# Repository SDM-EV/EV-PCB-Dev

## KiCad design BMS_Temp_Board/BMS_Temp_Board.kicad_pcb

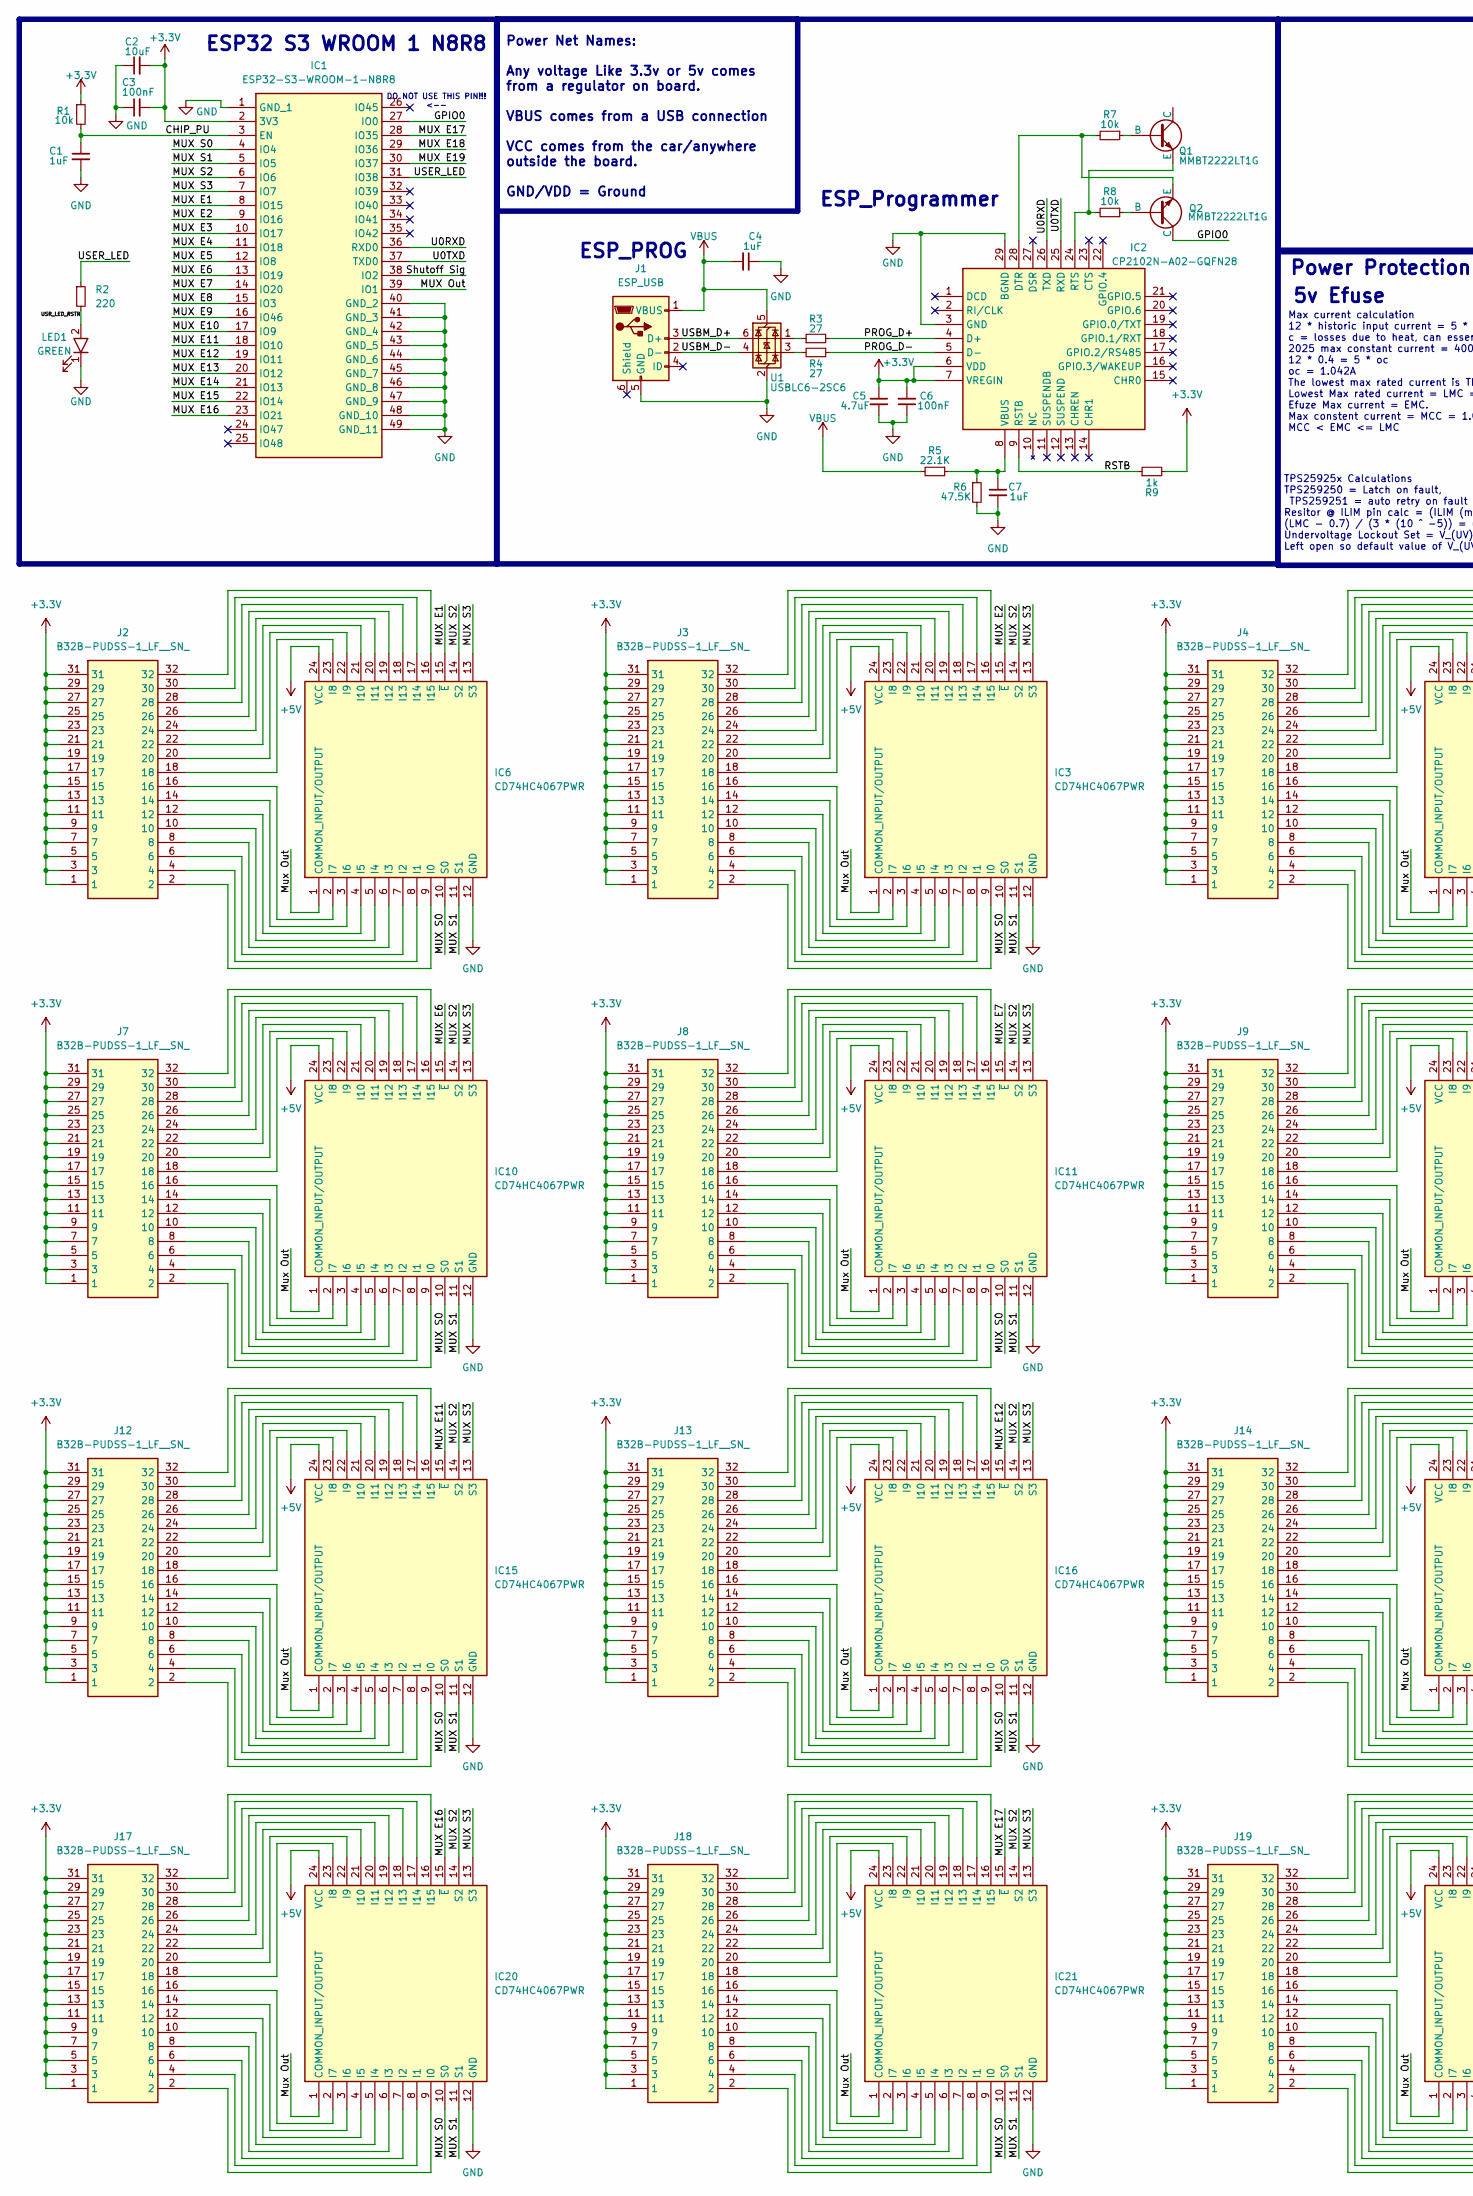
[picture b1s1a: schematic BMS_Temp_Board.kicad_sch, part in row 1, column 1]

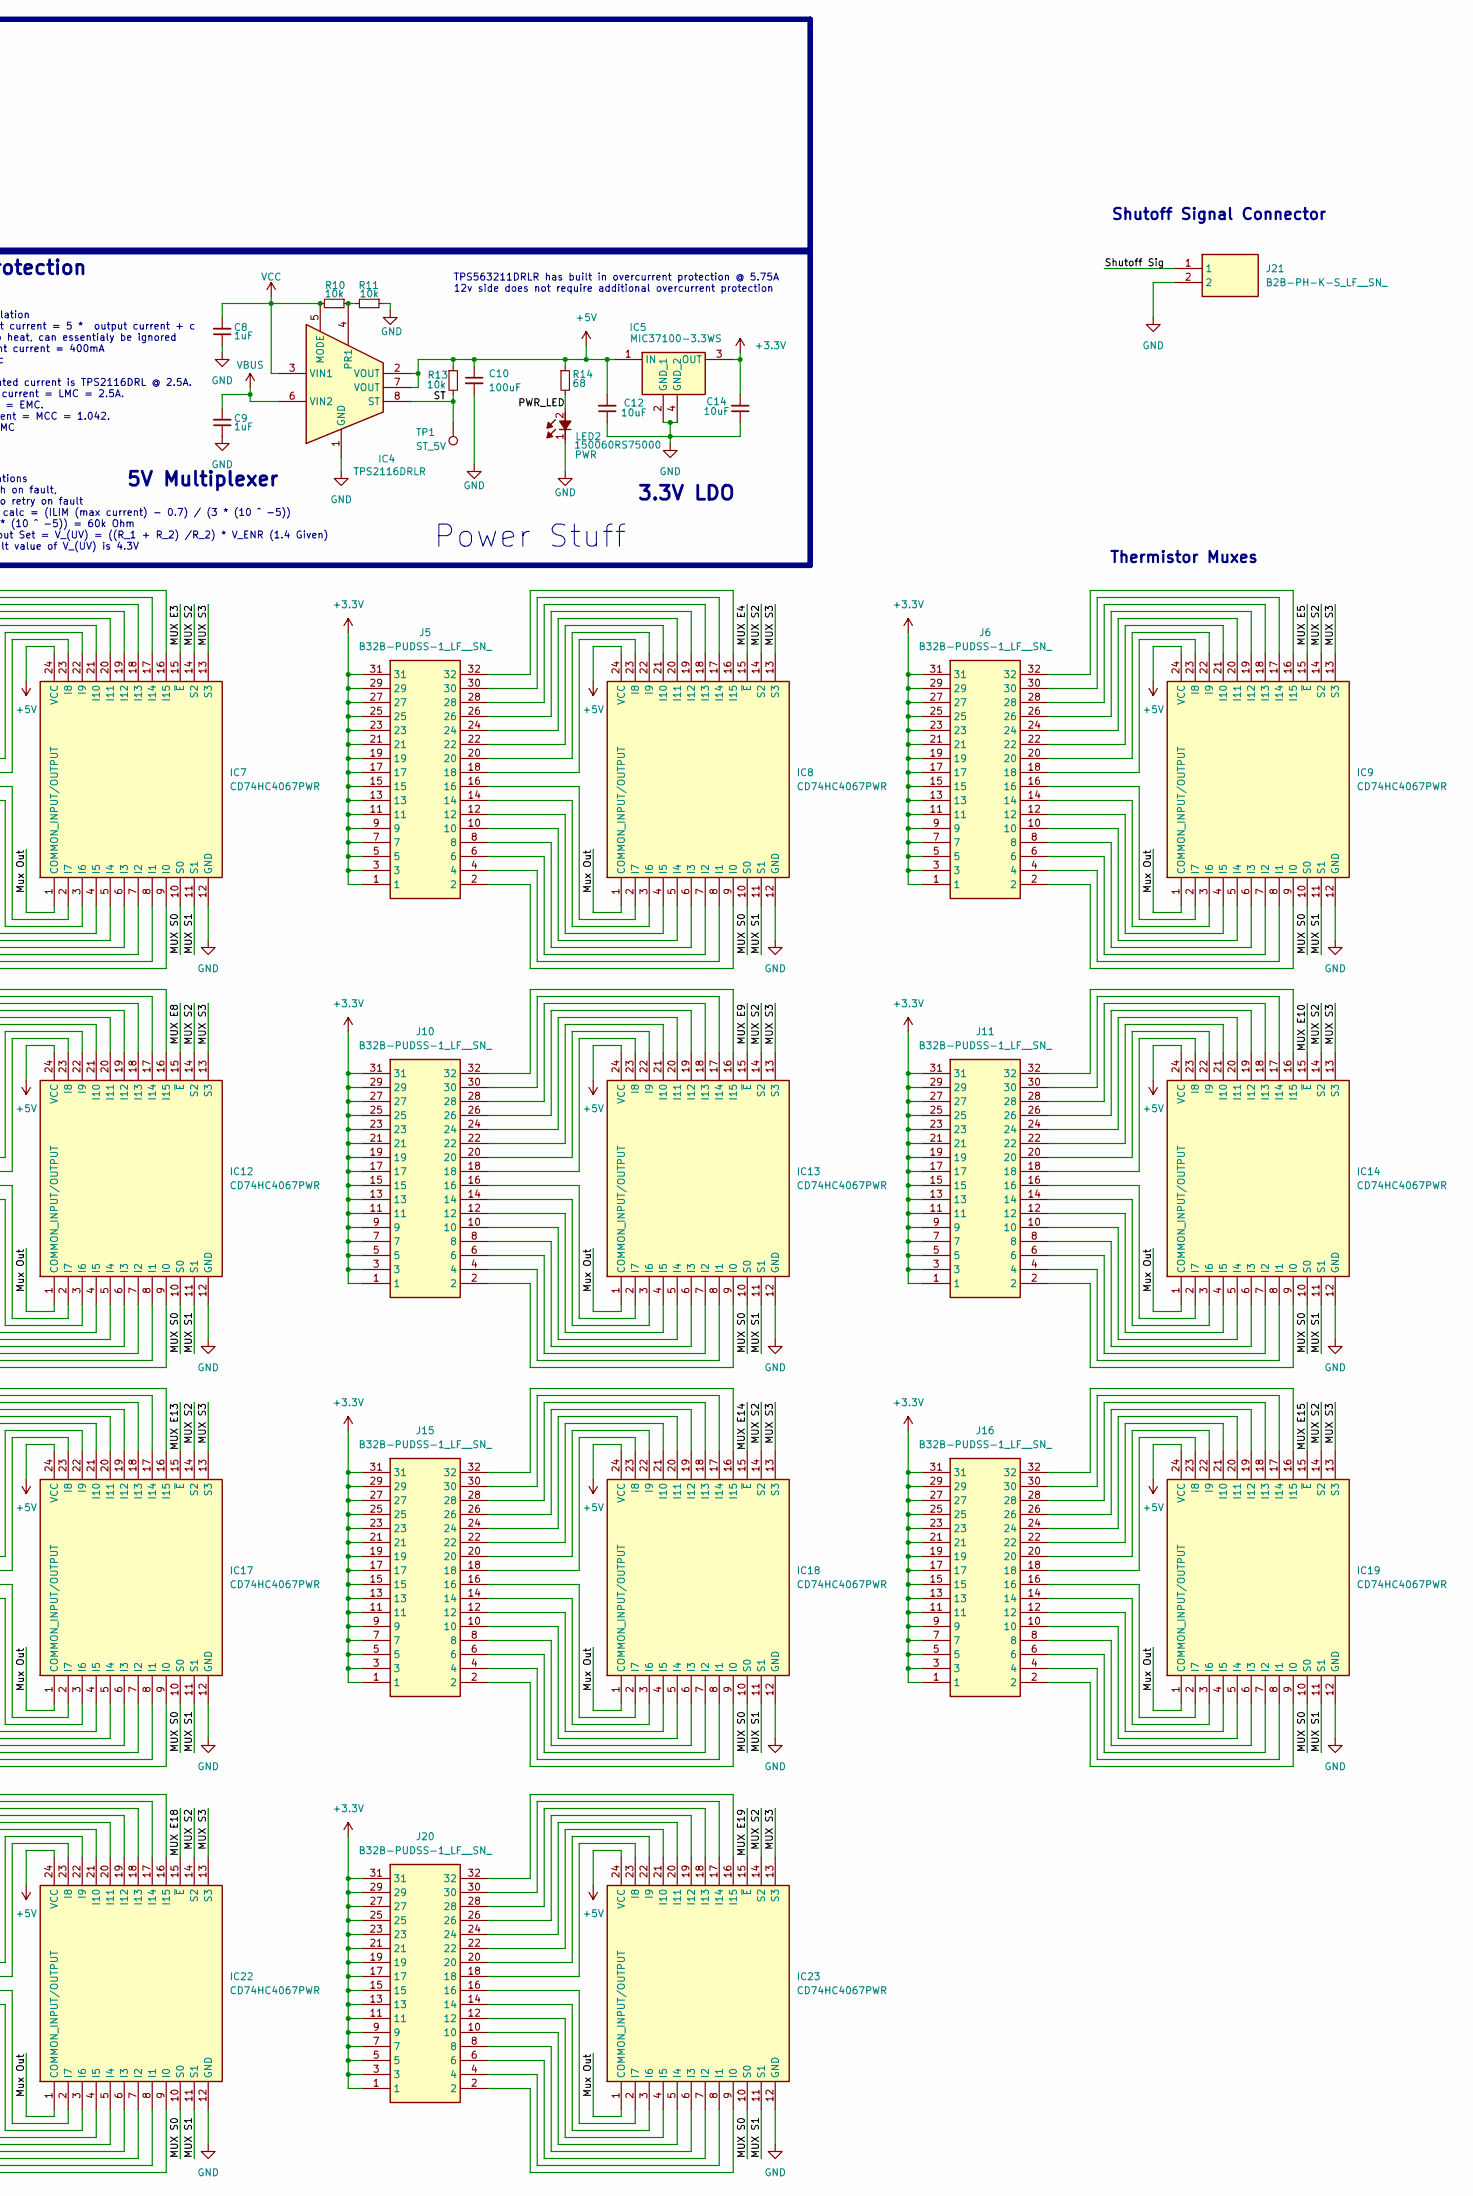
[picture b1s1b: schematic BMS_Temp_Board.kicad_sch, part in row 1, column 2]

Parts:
C1, C4, C7, C8, C9: 1uF; C_0603_1608Metric
C2, C12, C14: 10uF; C_0603_1608Metric
C3, C6: 100nF; C_0603_1608Metric
C5: 4.7uF; C_0603_1608Metric
C10: 100uF; C_0603_1608Metric
IC1: ESP32-S3-WROOM-1-N8R8; ESP32S3WROOM1N8R8; Mouser Part Number 356-EP32S3WROOM1N8R8
IC2: CP2102N-A02-GQFN28; QFN50P500X500X80-29N-D; Mouser Part Number 634-CP2102NA02GQFN28
IC3, IC6, IC7, IC8, IC9, IC10, IC11, IC12, IC13, IC14, IC15, IC16, IC17, IC18, IC19, IC20, IC21, IC22, IC23: CD74HC4067PWR; SOP65P640X120-24N; Manufacturer_Part_Number CD74HC4067PWR
IC4: TPS2116DRLR; SOTFL50P160X60-8L; Mouser Part Number 595-TPS2116DRLR
IC5: MIC37100-3.3WS; SOT230P700X180-4N; Mouser Part Number 998-MIC37100-3.3WS
J1: ESP_USB; USB_Micro-B_Molex-105017-0001
J2, J3, J4, J5, J6, J7, J8, J9, J10, J11, J12, J13, J14, J15, J16, J17, J18, J19, J20: B32B-PUDSS-1_LF__SN_; B32BPUDSS1LFSN; Mouser Part Number 306-B32BPUDSS1LFSN
J21: B2B-PH-K-S_LF__SN_; SHDR2W50P0X200_1X2_590X450X600P; Mouser Part Number 306-B2BPHKSLFSNPP
LED1: GREEN; LED_0603_1608Metric; Mouser Part Number 720-P4112S2U1252X4X5
LED2: 150060RS75000; LEDC1608X80N; Mouser Part Number 710-150060RS75000
Q1, Q2: MMBT2222LT1G; SOT96P237X111-3N
R1, R7, R8, R10, R11, R13: 10k; R_0603_1608Metric
R2: 220; R_0603_1608Metric
R3, R4: 27; R_0603_1608Metric
R5: 22.1K; R_0603_1608Metric
R6: 47.5K; R_0603_1608Metric
R9: 1k; R_0603_1608Metric
R14: 68; R_0603_1608Metric
TP1: ST_5V; TestPoint_Pad_1.5x1.5mm
U1: USBLC6-2SC6; SOT-23-6

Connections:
+3.3V: C2.2, C3.2, C5.1, C6.2, C14.2, IC1.2 (3V3), IC2.6 (VDD), IC2.7 (VREGIN), IC5.3 (OUT), J2.1, J2.3, J2.5, J2.7, J2.9, J2.11, J2.13, J2.15, J2.17, J2.19, J2.21, J2.23, J2.25, J2.27, J2.29, J2.31, J3.1, J3.3, J3.5, J3.7, J3.9, J3.11, J3.13, J3.15, J3.17, J3.19, J3.21, J3.23, J3.25, J3.27, J3.29, J3.31, J4.1, J4.3, J4.5, J4.7, J4.9, J4.11, J4.13, J4.15, J4.17, J4.19, J4.21, J4.23, J4.25, J4.27, J4.29, J4.31, J5.1, J5.3, J5.5, J5.7, J5.9, J5.11, J5.13, J5.15, J5.17, J5.19, J5.21, J5.23, J5.25, J5.27, J5.29, J5.31, J6.1, J6.3, J6.5, J6.7, J6.9, J6.11, J6.13, J6.15, J6.17, J6.19, J6.21, J6.23, J6.25, J6.27, J6.29, J6.31, J7.1, J7.3, J7.5, J7.7, J7.9, J7.11, J7.13, J7.15, J7.17, J7.19, J7.21, J7.23, J7.25, J7.27, J7.29, J7.31, J8.1, J8.3, J8.5, J8.7, J8.9, J8.11, J8.13, J8.15, J8.17, J8.19, J8.21, J8.23, J8.25, J8.27, J8.29, J8.31, J9.1, J9.3, J9.5, J9.7, J9.9, J9.11, J9.13, J9.15, J9.17, J9.19, J9.21, J9.23, J9.25, J9.27, J9.29, J9.31, J10.1, J10.3, J10.5, J10.7, J10.9, J10.11, J10.13, J10.15, J10.17, J10.19, J10.21, J10.23, J10.25, J10.27, J10.29, J10.31, J11.1, J11.3, J11.5, J11.7, J11.9, J11.11, J11.13, J11.15, J11.17, J11.19, J11.21, J11.23, J11.25, J11.27, J11.29, J11.31, J12.1, J12.3, J12.5, J12.7, J12.9, J12.11, J12.13, J12.15, J12.17, J12.19, J12.21, J12.23, J12.25, J12.27, J12.29, J12.31, J13.1, J13.3, J13.5, J13.7, J13.9, J13.11, J13.13, J13.15, J13.17, J13.19, J13.21, J13.23, J13.25, J13.27, J13.29, J13.31, J14.1, J14.3, J14.5, J14.7, J14.9, J14.11, J14.13, J14.15, J14.17, J14.19, J14.21, J14.23, J14.25, J14.27, J14.29, J14.31, J15.1, J15.3, J15.5, J15.7, J15.9, J15.11, J15.13, J15.15, J15.17, J15.19, J15.21, J15.23, J15.25, J15.27, J15.29, J15.31, J16.1, J16.3, J16.5, J16.7, J16.9, J16.11, J16.13, J16.15, J16.17, J16.19, J16.21, J16.23, J16.25, J16.27, J16.29, J16.31, J17.1, J17.3, J17.5, J17.7, J17.9, J17.11, J17.13, J17.15, J17.17, J17.19, J17.21, J17.23, J17.25, J17.27, J17.29, J17.31, J18.1, J18.3, J18.5, J18.7, J18.9, J18.11, J18.13, J18.15, J18.17, J18.19, J18.21, J18.23, J18.25, J18.27, J18.29, J18.31, J19.1, J19.3, J19.5, J19.7, J19.9, J19.11, J19.13, J19.15, J19.17, J19.19, J19.21, J19.23, J19.25, J19.27, J19.29, J19.31, J20.1, J20.3, J20.5, J20.7, J20.9, J20.11, J20.13, J20.15, J20.17, J20.19, J20.21, J20.23, J20.25, J20.27, J20.29, J20.31, R1.1, R9.2
+5V: C10.1, C12.2, IC3.24 (VCC), IC4.2 (VOUT), IC4.7 (VOUT), IC5.1 (IN), IC6.24 (VCC), IC7.24 (VCC), IC8.24 (VCC), IC9.24 (VCC), IC10.24 (VCC), IC11.24 (VCC), IC12.24 (VCC), IC13.24 (VCC), IC14.24 (VCC), IC15.24 (VCC), IC16.24 (VCC), IC17.24 (VCC), IC18.24 (VCC), IC19.24 (VCC), IC20.24 (VCC), IC21.24 (VCC), IC22.24 (VCC), IC23.24 (VCC), R13.1, R14.1
/CHIP_PU: C1.1, IC1.3 (EN), R1.2
/GPIO0: IC1.27 (IO0), Q2.3 (C)
/MUX E1: IC1.8 (IO15), IC6.15 (~E)
/MUX E2: IC1.9 (IO16), IC3.15 (~E)
/MUX E3: IC1.10 (IO17), IC7.15 (~E)
/MUX E4: IC1.11 (IO18), IC8.15 (~E)
/MUX E5: IC1.12 (IO8), IC9.15 (~E)
/MUX E6: IC1.13 (IO19), IC10.15 (~E)
/MUX E7: IC1.14 (IO20), IC11.15 (~E)
/MUX E8: IC1.15 (IO3), IC12.15 (~E)
/MUX E9: IC1.16 (IO46), IC13.15 (~E)
/MUX E10: IC1.17 (IO9), IC14.15 (~E)
/MUX E11: IC1.18 (IO10), IC15.15 (~E)
/MUX E12: IC1.19 (IO11), IC16.15 (~E)
/MUX E13: IC1.20 (IO12), IC17.15 (~E)
/MUX E14: IC1.21 (IO13), IC18.15 (~E)
/MUX E15: IC1.22 (IO14), IC19.15 (~E)
/MUX E16: IC1.23 (IO21), IC20.15 (~E)
/MUX E17: IC1.28 (IO35), IC21.15 (~E)
/MUX E18: IC1.29 (IO36), IC22.15 (~E)
/MUX E19: IC1.30 (IO37), IC23.15 (~E)
/MUX Out: IC1.39 (IO1)
/MUX S0: IC1.4 (IO4), IC3.10 (S0), IC6.10 (S0), IC7.10 (S0), IC8.10 (S0), IC9.10 (S0), IC10.10 (S0), IC11.10 (S0), IC12.10 (S0), IC13.10 (S0), IC14.10 (S0), IC15.10 (S0), IC16.10 (S0), IC17.10 (S0), IC18.10 (S0), IC19.10 (S0), IC20.10 (S0), IC21.10 (S0), IC22.10 (S0), IC23.10 (S0)
/MUX S1: IC1.5 (IO5), IC3.11 (S1), IC6.11 (S1), IC7.11 (S1), IC8.11 (S1), IC9.11 (S1), IC10.11 (S1), IC11.11 (S1), IC12.11 (S1), IC13.11 (S1), IC14.11 (S1), IC15.11 (S1), IC16.11 (S1), IC17.11 (S1), IC18.11 (S1), IC19.11 (S1), IC20.11 (S1), IC21.11 (S1), IC22.11 (S1), IC23.11 (S1)
/MUX S2: IC1.6 (IO6), IC3.14 (S2), IC6.14 (S2), IC7.14 (S2), IC8.14 (S2), IC9.14 (S2), IC10.14 (S2), IC11.14 (S2), IC12.14 (S2), IC13.14 (S2), IC14.14 (S2), IC15.14 (S2), IC16.14 (S2), IC17.14 (S2), IC18.14 (S2), IC19.14 (S2), IC20.14 (S2), IC21.14 (S2), IC22.14 (S2), IC23.14 (S2)
/MUX S3: IC1.7 (IO7), IC3.13 (S3), IC6.13 (S3), IC7.13 (S3), IC8.13 (S3), IC9.13 (S3), IC10.13 (S3), IC11.13 (S3), IC12.13 (S3), IC13.13 (S3), IC14.13 (S3), IC15.13 (S3), IC16.13 (S3), IC17.13 (S3), IC18.13 (S3), IC19.13 (S3), IC20.13 (S3), IC21.13 (S3), IC22.13 (S3), IC23.13 (S3)
/Mux Out: IC3.1 (COMMON_INPUT/OUTPUT), IC6.1 (COMMON_INPUT/OUTPUT), IC7.1 (COMMON_INPUT/OUTPUT), IC8.1 (COMMON_INPUT/OUTPUT), IC9.1 (COMMON_INPUT/OUTPUT), IC10.1 (COMMON_INPUT/OUTPUT), IC11.1 (COMMON_INPUT/OUTPUT), IC12.1 (COMMON_INPUT/OUTPUT), IC13.1 (COMMON_INPUT/OUTPUT), IC14.1 (COMMON_INPUT/OUTPUT), IC15.1 (COMMON_INPUT/OUTPUT), IC16.1 (COMMON_INPUT/OUTPUT), IC17.1 (COMMON_INPUT/OUTPUT), IC18.1 (COMMON_INPUT/OUTPUT), IC19.1 (COMMON_INPUT/OUTPUT), IC20.1 (COMMON_INPUT/OUTPUT), IC21.1 (COMMON_INPUT/OUTPUT), IC22.1 (COMMON_INPUT/OUTPUT), IC23.1 (COMMON_INPUT/OUTPUT)
/PROG_D+: IC2.4 (D+), R3.2
/PROG_D-: IC2.5 (D-), R4.1
/PWR_LED: LED2.2 (A), R14.2
/RSTB: IC2.9 (RSTB), R9.1
/ST: IC4.8 (ST), R13.2, TP1.1
/Shutoff Sig: IC1.38 (IO2), J21.1
/U0RXD: IC1.36 (RXD0), IC2.26 (TXD)
/U0TXD: IC1.37 (TXD0), IC2.25 (RXD)
/USBM_D+: J1.3 (D+), U1.6 (I/O1)
/USBM_D-: J1.2 (D-), U1.4 (I/O2)
/USER_LED: IC1.31 (IO38), R2.1
/USR_LED_RSTR: LED1.2 (A), R2.2
GND: C1.2, C2.1, C3.1, C4.1, C5.2, C6.1, C7.2, C8.1, C9.1, C10.2, C12.1, C14.1, IC1.1 (GND_1), IC1.40 (GND_2), IC1.41 (GND_3), IC1.42 (GND_4), IC1.43 (GND_5), IC1.44 (GND_6), IC1.45 (GND_7), IC1.46 (GND_8), IC1.47 (GND_9), IC1.48 (GND_10), IC1.49 (GND_11), IC2.3 (GND), IC2.29 (BGND), IC3.12 (GND), IC4.1 (GND), IC5.2 (GND_1), IC5.4 (GND_2), IC6.12 (GND), IC7.12 (GND), IC8.12 (GND), IC9.12 (GND), IC10.12 (GND), IC11.12 (GND), IC12.12 (GND), IC13.12 (GND), IC14.12 (GND), IC15.12 (GND), IC16.12 (GND), IC17.12 (GND), IC18.12 (GND), IC19.12 (GND), IC20.12 (GND), IC21.12 (GND), IC22.12 (GND), IC23.12 (GND), J1.5 (GND), J21.2, LED1.1 (K), LED2.1 (K), R6.2, R11.1, U1.2 (GND)
unnamed: IC2.28 (DTR), Q2.2 (E), R7.2
unnamed: IC2.24 (RTS), Q1.2 (E), R8.2
unnamed: C7.1, IC2.8 (VBUS), R5.1, R6.1
unnamed: IC3.9 (I0), J3.2
unnamed: IC3.8 (I1), J3.4
unnamed: IC3.7 (I2), J3.6
unnamed: IC3.6 (I3), J3.8
unnamed: IC3.5 (I4), J3.10
unnamed: IC3.4 (I5), J3.12
unnamed: IC3.3 (I6), J3.14
unnamed: IC3.2 (I7), J3.16
unnamed: IC3.23 (I8), J3.18
unnamed: IC3.22 (I9), J3.20
unnamed: IC3.21 (I10), J3.22
unnamed: IC3.20 (I11), J3.24
unnamed: IC3.19 (I12), J3.26
unnamed: IC3.18 (I13), J3.28
unnamed: IC3.17 (I14), J3.30
unnamed: IC3.16 (I15), J3.32
unnamed: IC4.4 (PR1), R10.1, R11.2
unnamed: IC6.9 (I0), J2.2
unnamed: IC6.8 (I1), J2.4
unnamed: IC6.7 (I2), J2.6
unnamed: IC6.6 (I3), J2.8
unnamed: IC6.5 (I4), J2.10
unnamed: IC6.4 (I5), J2.12
unnamed: IC6.3 (I6), J2.14
unnamed: IC6.2 (I7), J2.16
unnamed: IC6.23 (I8), J2.18
unnamed: IC6.22 (I9), J2.20
unnamed: IC6.21 (I10), J2.22
unnamed: IC6.20 (I11), J2.24
unnamed: IC6.19 (I12), J2.26
unnamed: IC6.18 (I13), J2.28
unnamed: IC6.17 (I14), J2.30
unnamed: IC6.16 (I15), J2.32
unnamed: IC7.9 (I0), J4.2
unnamed: IC7.8 (I1), J4.4
unnamed: IC7.7 (I2), J4.6
unnamed: IC7.6 (I3), J4.8
unnamed: IC7.5 (I4), J4.10
unnamed: IC7.4 (I5), J4.12
unnamed: IC7.3 (I6), J4.14
unnamed: IC7.2 (I7), J4.16
unnamed: IC7.23 (I8), J4.18
unnamed: IC7.22 (I9), J4.20
unnamed: IC7.21 (I10), J4.22
unnamed: IC7.20 (I11), J4.24
unnamed: IC7.19 (I12), J4.26
unnamed: IC7.18 (I13), J4.28
unnamed: IC7.17 (I14), J4.30
unnamed: IC7.16 (I15), J4.32
unnamed: IC8.9 (I0), J5.2
unnamed: IC8.8 (I1), J5.4
unnamed: IC8.7 (I2), J5.6
unnamed: IC8.6 (I3), J5.8
unnamed: IC8.5 (I4), J5.10
unnamed: IC8.4 (I5), J5.12
unnamed: IC8.3 (I6), J5.14
unnamed: IC8.2 (I7), J5.16
unnamed: IC8.23 (I8), J5.18
unnamed: IC8.22 (I9), J5.20
unnamed: IC8.21 (I10), J5.22
unnamed: IC8.20 (I11), J5.24
unnamed: IC8.19 (I12), J5.26
unnamed: IC8.18 (I13), J5.28
unnamed: IC8.17 (I14), J5.30
unnamed: IC8.16 (I15), J5.32
unnamed: IC9.9 (I0), J6.2
unnamed: IC9.8 (I1), J6.4
unnamed: IC9.7 (I2), J6.6
unnamed: IC9.6 (I3), J6.8
unnamed: IC9.5 (I4), J6.10
unnamed: IC9.4 (I5), J6.12
unnamed: IC9.3 (I6), J6.14
unnamed: IC9.2 (I7), J6.16
unnamed: IC9.23 (I8), J6.18
unnamed: IC9.22 (I9), J6.20
unnamed: IC9.21 (I10), J6.22
unnamed: IC9.20 (I11), J6.24
unnamed: IC9.19 (I12), J6.26
unnamed: IC9.18 (I13), J6.28
unnamed: IC9.17 (I14), J6.30
unnamed: IC9.16 (I15), J6.32
unnamed: IC10.9 (I0), J7.2
unnamed: IC10.8 (I1), J7.4
unnamed: IC10.7 (I2), J7.6
unnamed: IC10.6 (I3), J7.8
unnamed: IC10.5 (I4), J7.10
unnamed: IC10.4 (I5), J7.12
unnamed: IC10.3 (I6), J7.14
unnamed: IC10.2 (I7), J7.16
unnamed: IC10.23 (I8), J7.18
unnamed: IC10.22 (I9), J7.20
unnamed: IC10.21 (I10), J7.22
unnamed: IC10.20 (I11), J7.24
unnamed: IC10.19 (I12), J7.26
unnamed: IC10.18 (I13), J7.28
unnamed: IC10.17 (I14), J7.30
unnamed: IC10.16 (I15), J7.32
unnamed: IC11.9 (I0), J8.2
unnamed: IC11.8 (I1), J8.4
unnamed: IC11.7 (I2), J8.6
unnamed: IC11.6 (I3), J8.8
unnamed: IC11.5 (I4), J8.10
unnamed: IC11.4 (I5), J8.12
unnamed: IC11.3 (I6), J8.14
unnamed: IC11.2 (I7), J8.16
unnamed: IC11.23 (I8), J8.18
unnamed: IC11.22 (I9), J8.20
unnamed: IC11.21 (I10), J8.22
unnamed: IC11.20 (I11), J8.24
unnamed: IC11.19 (I12), J8.26
unnamed: IC11.18 (I13), J8.28
unnamed: IC11.17 (I14), J8.30
unnamed: IC11.16 (I15), J8.32
unnamed: IC12.9 (I0), J9.2
unnamed: IC12.8 (I1), J9.4
unnamed: IC12.7 (I2), J9.6
unnamed: IC12.6 (I3), J9.8
unnamed: IC12.5 (I4), J9.10
unnamed: IC12.4 (I5), J9.12
unnamed: IC12.3 (I6), J9.14
unnamed: IC12.2 (I7), J9.16
unnamed: IC12.23 (I8), J9.18
unnamed: IC12.22 (I9), J9.20
unnamed: IC12.21 (I10), J9.22
unnamed: IC12.20 (I11), J9.24
unnamed: IC12.19 (I12), J9.26
unnamed: IC12.18 (I13), J9.28
unnamed: IC12.17 (I14), J9.30
unnamed: IC12.16 (I15), J9.32
unnamed: IC13.9 (I0), J10.2
unnamed: IC13.8 (I1), J10.4
unnamed: IC13.7 (I2), J10.6
unnamed: IC13.6 (I3), J10.8
unnamed: IC13.5 (I4), J10.10
unnamed: IC13.4 (I5), J10.12
unnamed: IC13.3 (I6), J10.14
unnamed: IC13.2 (I7), J10.16
unnamed: IC13.23 (I8), J10.18
unnamed: IC13.22 (I9), J10.20
unnamed: IC13.21 (I10), J10.22
unnamed: IC13.20 (I11), J10.24
unnamed: IC13.19 (I12), J10.26
unnamed: IC13.18 (I13), J10.28
unnamed: IC13.17 (I14), J10.30
unnamed: IC13.16 (I15), J10.32
unnamed: IC14.9 (I0), J11.2
unnamed: IC14.8 (I1), J11.4
unnamed: IC14.7 (I2), J11.6
unnamed: IC14.6 (I3), J11.8
unnamed: IC14.5 (I4), J11.10
unnamed: IC14.4 (I5), J11.12
unnamed: IC14.3 (I6), J11.14
unnamed: IC14.2 (I7), J11.16
unnamed: IC14.23 (I8), J11.18
unnamed: IC14.22 (I9), J11.20
unnamed: IC14.21 (I10), J11.22
unnamed: IC14.20 (I11), J11.24
unnamed: IC14.19 (I12), J11.26
unnamed: IC14.18 (I13), J11.28
unnamed: IC14.17 (I14), J11.30
unnamed: IC14.16 (I15), J11.32
unnamed: IC15.9 (I0), J12.2
unnamed: IC15.8 (I1), J12.4
unnamed: IC15.7 (I2), J12.6
unnamed: IC15.6 (I3), J12.8
unnamed: IC15.5 (I4), J12.10
unnamed: IC15.4 (I5), J12.12
unnamed: IC15.3 (I6), J12.14
unnamed: IC15.2 (I7), J12.16
unnamed: IC15.23 (I8), J12.18
unnamed: IC15.22 (I9), J12.20
unnamed: IC15.21 (I10), J12.22
unnamed: IC15.20 (I11), J12.24
unnamed: IC15.19 (I12), J12.26
unnamed: IC15.18 (I13), J12.28
unnamed: IC15.17 (I14), J12.30
unnamed: IC15.16 (I15), J12.32
unnamed: IC16.9 (I0), J13.2
unnamed: IC16.8 (I1), J13.4
unnamed: IC16.7 (I2), J13.6
unnamed: IC16.6 (I3), J13.8
unnamed: IC16.5 (I4), J13.10
unnamed: IC16.4 (I5), J13.12
unnamed: IC16.3 (I6), J13.14
unnamed: IC16.2 (I7), J13.16
unnamed: IC16.23 (I8), J13.18
unnamed: IC16.22 (I9), J13.20
unnamed: IC16.21 (I10), J13.22
unnamed: IC16.20 (I11), J13.24
unnamed: IC16.19 (I12), J13.26
unnamed: IC16.18 (I13), J13.28
unnamed: IC16.17 (I14), J13.30
unnamed: IC16.16 (I15), J13.32
unnamed: IC17.9 (I0), J14.2
unnamed: IC17.8 (I1), J14.4
unnamed: IC17.7 (I2), J14.6
unnamed: IC17.6 (I3), J14.8
unnamed: IC17.5 (I4), J14.10
unnamed: IC17.4 (I5), J14.12
unnamed: IC17.3 (I6), J14.14
unnamed: IC17.2 (I7), J14.16
unnamed: IC17.23 (I8), J14.18
unnamed: IC17.22 (I9), J14.20
unnamed: IC17.21 (I10), J14.22
unnamed: IC17.20 (I11), J14.24
unnamed: IC17.19 (I12), J14.26
unnamed: IC17.18 (I13), J14.28
unnamed: IC17.17 (I14), J14.30
unnamed: IC17.16 (I15), J14.32
unnamed: IC18.9 (I0), J15.2
unnamed: IC18.8 (I1), J15.4
unnamed: IC18.7 (I2), J15.6
unnamed: IC18.6 (I3), J15.8
unnamed: IC18.5 (I4), J15.10
unnamed: IC18.4 (I5), J15.12
unnamed: IC18.3 (I6), J15.14
unnamed: IC18.2 (I7), J15.16
unnamed: IC18.23 (I8), J15.18
unnamed: IC18.22 (I9), J15.20
unnamed: IC18.21 (I10), J15.22
unnamed: IC18.20 (I11), J15.24
unnamed: IC18.19 (I12), J15.26
unnamed: IC18.18 (I13), J15.28
unnamed: IC18.17 (I14), J15.30
unnamed: IC18.16 (I15), J15.32
unnamed: IC19.9 (I0), J16.2
unnamed: IC19.8 (I1), J16.4
unnamed: IC19.7 (I2), J16.6
unnamed: IC19.6 (I3), J16.8
unnamed: IC19.5 (I4), J16.10
unnamed: IC19.4 (I5), J16.12
unnamed: IC19.3 (I6), J16.14
unnamed: IC19.2 (I7), J16.16
unnamed: IC19.23 (I8), J16.18
unnamed: IC19.22 (I9), J16.20
unnamed: IC19.21 (I10), J16.22
unnamed: IC19.20 (I11), J16.24
unnamed: IC19.19 (I12), J16.26
unnamed: IC19.18 (I13), J16.28
unnamed: IC19.17 (I14), J16.30
unnamed: IC19.16 (I15), J16.32
unnamed: IC20.9 (I0), J17.2
unnamed: IC20.8 (I1), J17.4
unnamed: IC20.7 (I2), J17.6
unnamed: IC20.6 (I3), J17.8
unnamed: IC20.5 (I4), J17.10
unnamed: IC20.4 (I5), J17.12
unnamed: IC20.3 (I6), J17.14
unnamed: IC20.2 (I7), J17.16
unnamed: IC20.23 (I8), J17.18
unnamed: IC20.22 (I9), J17.20
unnamed: IC20.21 (I10), J17.22
unnamed: IC20.20 (I11), J17.24
unnamed: IC20.19 (I12), J17.26
unnamed: IC20.18 (I13), J17.28
unnamed: IC20.17 (I14), J17.30
unnamed: IC20.16 (I15), J17.32
unnamed: IC21.9 (I0), J18.2
unnamed: IC21.8 (I1), J18.4
unnamed: IC21.7 (I2), J18.6
unnamed: IC21.6 (I3), J18.8
unnamed: IC21.5 (I4), J18.10
unnamed: IC21.4 (I5), J18.12
unnamed: IC21.3 (I6), J18.14
unnamed: IC21.2 (I7), J18.16
unnamed: IC21.23 (I8), J18.18
unnamed: IC21.22 (I9), J18.20
unnamed: IC21.21 (I10), J18.22
unnamed: IC21.20 (I11), J18.24
unnamed: IC21.19 (I12), J18.26
unnamed: IC21.18 (I13), J18.28
unnamed: IC21.17 (I14), J18.30
unnamed: IC21.16 (I15), J18.32
unnamed: IC22.9 (I0), J19.2
unnamed: IC22.8 (I1), J19.4
unnamed: IC22.7 (I2), J19.6
unnamed: IC22.6 (I3), J19.8
unnamed: IC22.5 (I4), J19.10
unnamed: IC22.4 (I5), J19.12
unnamed: IC22.3 (I6), J19.14
unnamed: IC22.2 (I7), J19.16
unnamed: IC22.23 (I8), J19.18
unnamed: IC22.22 (I9), J19.20
unnamed: IC22.21 (I10), J19.22
unnamed: IC22.20 (I11), J19.24
unnamed: IC22.19 (I12), J19.26
unnamed: IC22.18 (I13), J19.28
unnamed: IC22.17 (I14), J19.30
unnamed: IC22.16 (I15), J19.32
unnamed: IC23.9 (I0), J20.2
unnamed: IC23.8 (I1), J20.4
unnamed: IC23.7 (I2), J20.6
unnamed: IC23.6 (I3), J20.8
unnamed: IC23.5 (I4), J20.10
unnamed: IC23.4 (I5), J20.12
unnamed: IC23.3 (I6), J20.14
unnamed: IC23.2 (I7), J20.16
unnamed: IC23.23 (I8), J20.18
unnamed: IC23.22 (I9), J20.20
unnamed: IC23.21 (I10), J20.22
unnamed: IC23.20 (I11), J20.24
unnamed: IC23.19 (I12), J20.26
unnamed: IC23.18 (I13), J20.28
unnamed: IC23.17 (I14), J20.30
unnamed: IC23.16 (I15), J20.32
unnamed: Q1.1 (B), R7.1
unnamed: Q2.1 (B), R8.1
unnamed: R3.1, U1.1 (I/O1)
unnamed: R4.2, U1.3 (I/O2)
VBUS: C4.2, C9.2, IC4.6 (VIN2), J1.1 (VBUS), R5.2, U1.5 (VBUS)
VCC: C8.2, IC4.3 (VIN1), IC4.5 (MODE), R10.2

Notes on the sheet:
Power Protection
Power Stuff
3.3V LDO
TPS563211DRLR has built in overcurrent protection @ 5.75A 12v side does not require additional overcurrent protection
Shutoff Signal Connector
5v Efuse
TPS25925x Calculations TPS259250 = Latch on fault, TPS259251 = auto retry on fault Resitor @ ILIM pin calc = (ILIM (max current) - 0.7) / (3 * (10 ^ -5)) (LMC - 0.7) / (3 * (10 ^ -5)) = 60k Ohm Undervoltage Lockout Set = V_(UV) = ((R_1 + R_2) /R_2) * V_ENR (1.4 Given) Left open so default value of 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
ESP_PROG
5V Multiplexer
DO NOT USE THIS PIN!!! <--
Thermistor Muxes
Max current calculation 12 * historic input current = 5 * output current + c c = losses due to heat, can essentialy be ignored 2025 max constant current = 400mA 12 * 0.4 = 5 * oc oc = 1.042A The lowest max rated current is TPS2116DRL @ 2.5A. Lowest Max rated current = LMC = 2.5A. Efuze Max current 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
ESP32 S3 WROOM 1 N8R8
ESP_Programmer
Power Net Names: Any voltage Like 3.3v or 5v comes from a regulator on board. VBUS comes from a USB connection VCC comes from the car/anywhere outside the board. GND/VDD = Ground

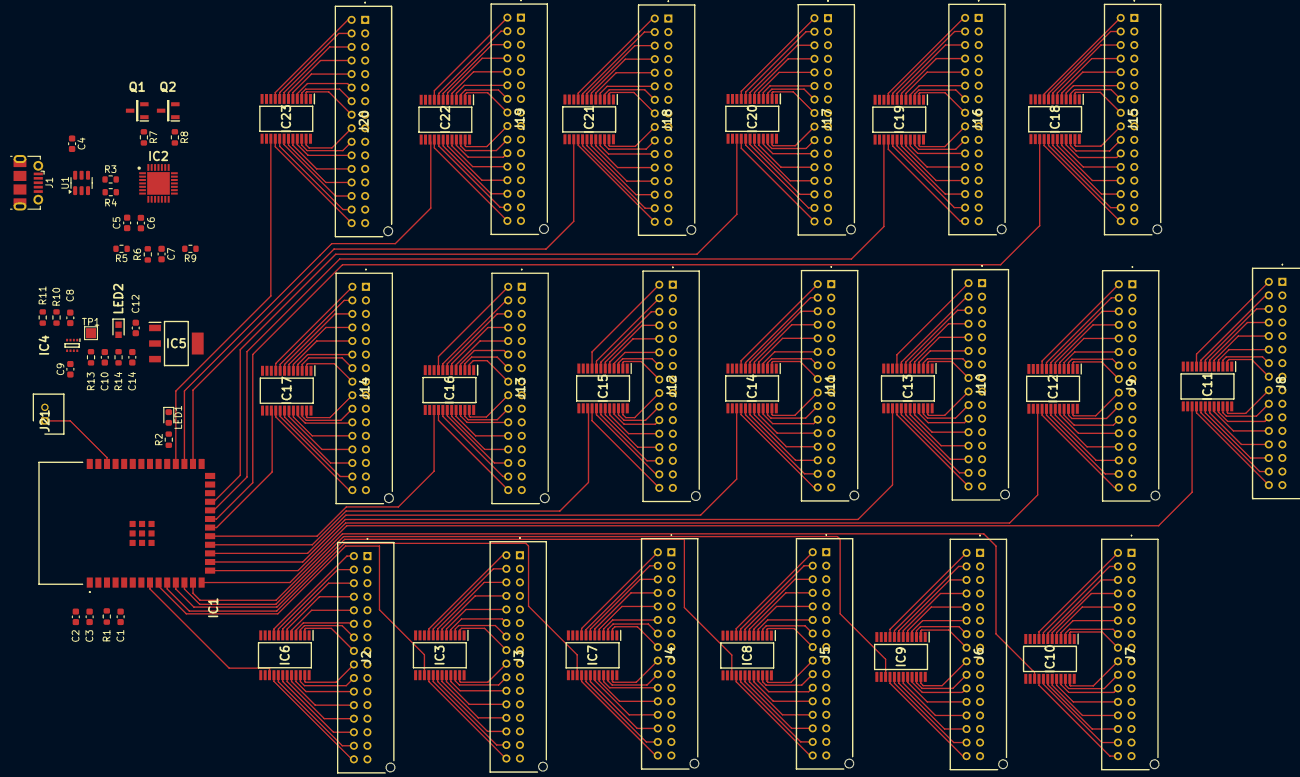
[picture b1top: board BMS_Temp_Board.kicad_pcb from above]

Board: 2 copper layers, 75 parts (0 on the bottom side), 355 nets.
